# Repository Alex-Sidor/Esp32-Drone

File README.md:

This drone is primarily being made as a integration with my motion tracking system

my drone is comprised of
* 4x 8520 brushless dc motors
* 4x props (came with dc motors)
* 1x custom pcb (file linked)
* 1x Esp32 Devkit C3 (you can use whatever esp you want)
* 1x mpu6050
* 1x 3.8V 95C battery
* assorted capacitors (read on where to put them)
* rubber spacers to remove vibration from the mpu6050 (get better readings)
* long m2 bolts and nuts to secure top part

for the drone frame i used

`https://www.thingiverse.com/thing:1221911`

Here is a picture of the designed pcb

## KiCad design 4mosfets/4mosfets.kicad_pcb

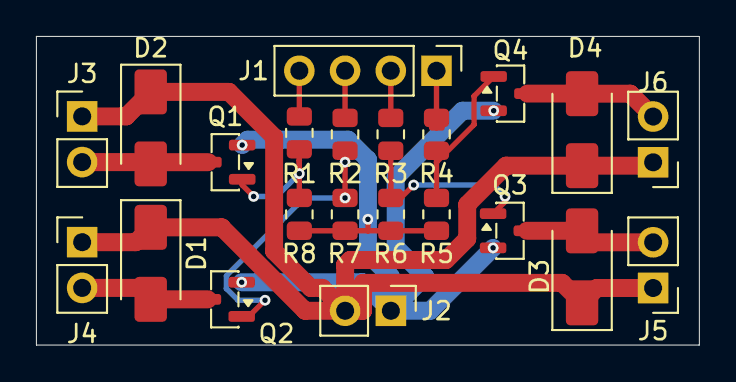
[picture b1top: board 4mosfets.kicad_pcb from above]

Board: 2 copper layers, 36.8 x 17.1 mm, 22 parts (0 on the bottom side), 14 nets.

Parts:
D1, D2, D3, D4: SS14; D_SMA
J1: Conn_01x04_Pin; PinHeader_1x04_P2.54mm_Vertical
J2, J3, J4, J5, J6: Conn_01x02_Pin; PinHeader_1x02_P2.54mm_Vertical
Q1, Q2, Q3, Q4: AO3400A; SOT-23
R1, R2, R3, R4: 220; R_0805_2012Metric
R5, R6, R7, R8: 10k; R_0805_2012Metric

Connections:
/<NO NET>: J2.1, Q1.2 (S), Q2.2 (S), Q3.2 (S), Q4.2 (S), R5.2, R6.2, R7.2, R8.2
unnamed: D1.2 (A), J4.2, Q2.3 (D)
unnamed: D1.1 (K), D2.1 (K), D3.1 (K), D4.1 (K), J2.2, J3.1, J4.1, J5.1, J6.1
unnamed: D2.2 (A), J3.2, Q1.3 (D)
unnamed: D3.2 (A), J5.2, Q3.3 (D)
unnamed: D4.2 (A), J6.2, Q4.3 (D)
unnamed: J1.1, R4.1
unnamed: J1.2, R3.1
unnamed: J1.3, R2.1
unnamed: J1.4, R1.1
unnamed: Q1.1 (G), R1.2, R8.1
unnamed: Q2.1 (G), R2.2, R7.1
unnamed: Q3.1 (G), R3.2, R6.1
unnamed: Q4.1 (G), R4.2, R5.1

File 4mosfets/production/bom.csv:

Designator,Footprint,Quantity,Value,LCSC Part #
"D1, D2, D3, D4",D_SMA,4,SS14,
J1,PinHeader_1x04_P2.54mm_Vertical,1,Conn_01x04_Pin,
"J2, J3, J4, J5, J6",PinHeader_1x02_P2.54mm_Vertical,5,Conn_01x02_Pin,
"Q1, Q2, Q3, Q4",SOT-23,4,AO3400A,
"R1, R2, R3, R4",0805,4,220,
"R5, R6, R7, R8",0805,4,10k,

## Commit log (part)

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2025-11-08 init
2026-02-05 Create LICENSE
2026-06-13 added driver pcb
2026-06-13 added gitignore and fixed readme
2026-06-19 updated pcb to have contacts closer to edge
